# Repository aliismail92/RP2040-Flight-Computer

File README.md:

# RP2040-Flight-Computer
This is a custom drone flight computer based on RP2040. The KiCad files are available in addition to the production files to be produced by JLC PCB.

The Flight computer has the following sensors:
  - MPU 6050 Inertia sensor
  - HMC5883L digital compass sensor
  - BMP280 pressure sensor

Other specified connectors that can be added:
  - SD-card connector at the bottom of the board
  - Two uart connectors for the Radio controller (tagged IBUS) and another for GPS (tagged GPS)
  - Broken GPIOs for NRF24L01 with proper pin locations

Additionally, the two I2C ports connected to the MPU6050 and BMP280 have the pins exposed for debugging purposes.

The board was produced and assembled by JLCPCB and working.

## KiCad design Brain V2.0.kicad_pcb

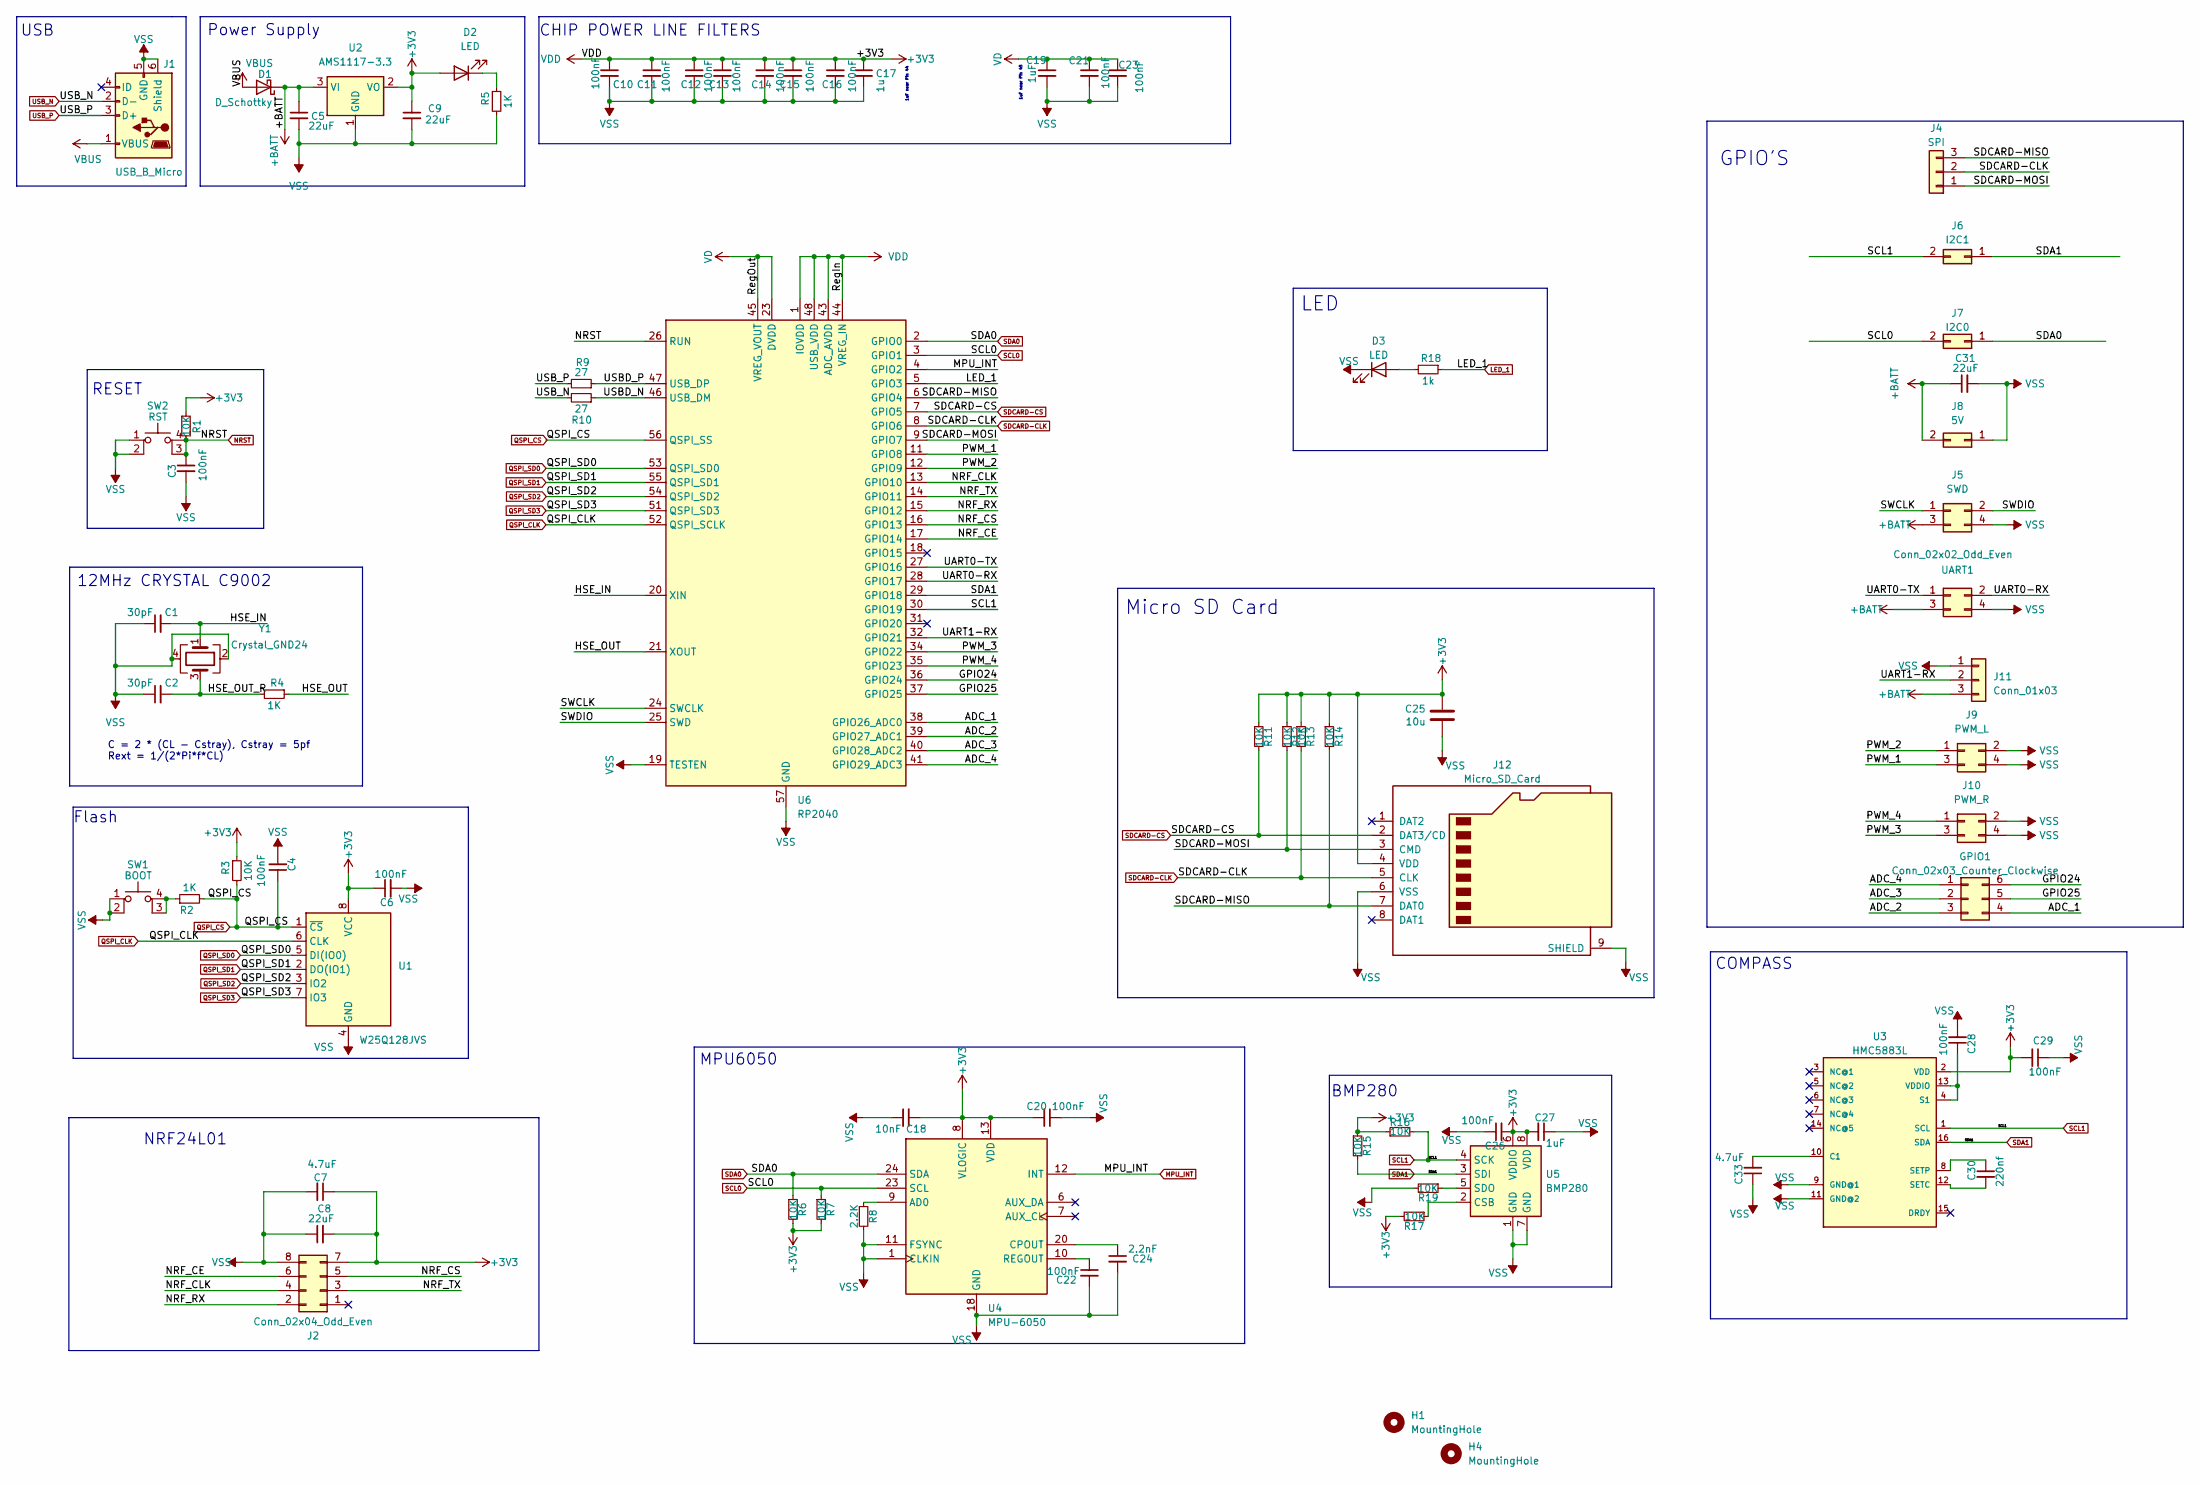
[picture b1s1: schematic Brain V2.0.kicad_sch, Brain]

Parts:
C1, C2: 30pF; C_0402_1005Metric
C3, C4, C6, C10, C11, C12, C13, C14, C15, C16, C20, C21, C22, C23, C26, C28, C29: 100nF; C_0402_1005Metric
C5, C8, C9, C31: 22uF; C_0603_1608Metric
C7, C33: 4.7uF; C_0603_1608Metric
C17: 1u; C_0402_1005Metric_Pad0.74x0.62mm_HandSolder
C18: 10nF; C_0402_1005Metric
C19: 1uF; C_0402_1005Metric_Pad0.74x0.62mm_HandSolder
C24: 2.2nF; C_0603_1608Metric
C25: 10u; C_0603_1608Metric
C27: 1uF; C_0402_1005Metric
C30: 220nf; C_0402_1005Metric
D1: D_Schottky; D_SMA
D2, D3: LED; LED_0603_1608Metric
GPIO1: Conn_02x03_Counter_Clockwise; PinHeader_2x03_P2.54mm_Vertical
H1, H4: MountingHole; MountingHole_4.3mm_M4
J1: USB_B_Micro; USB_Micro-B_Molex-105017-0001
J2: Conn_02x04_Odd_Even; PinHeader_2x04_P2.54mm_Vertical
J4: SPI; PinHeader_1x03_P2.54mm_Vertical
J5: SWD; PinHeader_2x02_P2.54mm_Vertical
J6: I2C1; PinHeader_2x01_P2.54mm_Vertical
J7: I2C0; PinHeader_2x01_P2.54mm_Vertical
J8: 5V; PinHeader_2x01_P2.54mm_Vertical
J9: PWM_L; PinHeader_2x02_P2.54mm_Vertical
J10: PWM_R; PinHeader_2x02_P2.54mm_Vertical
J11: Conn_01x03; JST_XH_B3B-XH-AM_1x03_P2.50mm_Vertical
J12: Micro_SD_Card; microSD_HC_Molex_104031-0811
R1, R3, R6, R7, R11, R12, R13, R14, R15, R16, R17, R19: 10K; R_0402_1005Metric
R2, R4: 1K; R_0402_1005Metric
R5: 1K; R_0603_1608Metric
R8: 2.2K; R_0402_1005Metric
R9, R10: 27; R_0603_1608Metric
R18: 1k; R_0603_1608Metric
SW1: BOOT; Button-01
SW2: RST; Button-01
U1: W25Q128JVS; SOIC-8_5.23x5.23mm_P1.27mm
U2: AMS1117-3.3; SOT-223-3_TabPin2
U3: HMC5883L; LPCC-16
U4: MPU-6050; InvenSense_QFN-24_4x4mm_P0.5mm_NoMask
U5: BMP280; Bosch_LGA-8_2x2.5mm_P0.65mm_ClockwisePinNumbering
U6: RP2040; QFN-56-1EP_7x7mm_P0.4mm_EP4x4mm_ThermalVias
UART1: Conn_02x02_Odd_Even; JST_XH_B4B-XH-A_1x04_P2.50mm_Vertical
Y1: Crystal_GND24; Crystal_SMD_3225-4Pin_3.2x2.5mm

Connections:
+3V3: C6.1, C7.1, C8.2, C9.1, C10.1, C11.1, C12.1, C13.1, C14.1, C15.1, C16.1, C17.1, C18.2, C20.2, C25.1, C26.2, C27.2, C29.2, D2.2 (A), J2.7, J12.4 (VDD), R1.1, R3.1, R6.2, R7.2, R11.1, R12.1, R13.1, R14.1, R15.1, R16.1, R17.2, U1.8 (VCC), U2.2 (VO), U3.2 (VDD), U4.8 (VLOGIC), U4.13 (VDD), U5.6 (VDDIO), U5.8 (VDD), U6.1 (IOVDD), U6.10 (IOVDD), U6.22 (IOVDD), U6.33 (IOVDD), U6.42 (IOVDD), U6.43 (ADC_AVDD), U6.44 (VREG_IN), U6.48 (USB_VDD), U6.49 (IOVDD)
+BATT: C5.1, C31.1, D1.1 (K), J5.3, J8.2, J11.3, U2.3 (VI), UART1.3
/ADC_1: GPIO1.4, U6.38 (GPIO26_ADC0)
/ADC_2: GPIO1.3, U6.39 (GPIO27_ADC1)
/ADC_3: GPIO1.2, U6.40 (GPIO28_ADC2)
/ADC_4: GPIO1.1, U6.41 (GPIO29_ADC3)
/GPIO24: GPIO1.6, U6.36 (GPIO24)
/GPIO25: GPIO1.5, U6.37 (GPIO25)
/HSE_IN: C1.2, U6.20 (XIN), Y1.1
/HSE_OUT: R4.1, U6.21 (XOUT)
/HSE_OUT_R: C2.2, R4.2, Y1.3
/NRF_CE: J2.6, U6.17 (GPIO14)
/NRF_CLK: J2.4, U6.13 (GPIO10)
/NRF_CS: J2.5, U6.16 (GPIO13)
/NRF_RX: J2.2, U6.15 (GPIO12)
/NRF_TX: J2.3, U6.14 (GPIO11)
/PWM_1: J9.3, U6.11 (GPIO8)
/PWM_2: J9.1, U6.12 (GPIO9)
/PWM_3: J10.3, U6.34 (GPIO22)
/PWM_4: J10.1, U6.35 (GPIO23)
/SDCARD-MISO: J4.3, J12.7 (DAT0), R14.2, U6.6 (GPIO4)
/SDCARD-MOSI: J4.1, J12.3 (CMD), R12.2, U6.9 (GPIO7)
/SWCLK: J5.1, U6.24 (SWCLK)
/SWDIO: J5.2, U6.25 (SWD)
/UART0-RX: U6.28 (GPIO17), UART1.2
/UART0-TX: U6.27 (GPIO16), UART1.1
/UART1-RX: J11.2, U6.32 (GPIO21)
/USBD_N: R10.1, U6.46 (USB_DM)
/USBD_P: R9.1, U6.47 (USB_DP)
LED_1: R18.1, U6.5 (GPIO3)
MPU_INT: U4.12 (INT), U6.4 (GPIO2)
NRST: C3.1, R1.2, SW2.3 (K), SW2.4 (A), U6.26 (RUN)
unnamed: D2.1 (K), R5.1
unnamed: D3.2 (A), R18.2
unnamed: R2.1, SW1.3 (K), SW1.4 (A)
unnamed: C33.2, U3.10 (C1)
unnamed: C28.1, U3.4 (S1), U3.13 (VDDIO)
unnamed: C30.2, U3.12 (SETC)
unnamed: C30.1, U3.8 (SETP)
unnamed: R8.1, U4.9 (AD0)
unnamed: C24.1, U4.20 (CPOUT)
unnamed: C22.1, U4.10 (REGOUT)
unnamed: R17.1, U5.2 (CSB)
unnamed: R19.1, U5.5 (SDO)
QSPI_CLK: U1.6 (CLK), U6.52 (QSPI_SCLK)
QSPI_CS: C4.1, R2.2, R3.2, U1.1 (~CS), U6.56 (QSPI_SS)
QSPI_SD0: U1.5 (DI(IO0)), U6.53 (QSPI_SD0)
QSPI_SD1: U1.2 (DO(IO1)), U6.55 (QSPI_SD1)
QSPI_SD2: U1.3 (IO2), U6.54 (QSPI_SD2)
QSPI_SD3: U1.7 (IO3), U6.51 (QSPI_SD3)
SCL0: J7.2, R7.1, U4.23 (SCL), U6.3 (GPIO1)
SCL1: J6.2, R16.2, U3.1 (SCL), U5.4 (SCK), U6.30 (GPIO19)
SDA0: J7.1, R6.1, U4.24 (SDA), U6.2 (GPIO0)
SDA1: J6.1, R15.2, U3.16 (SDA), U5.3 (SDI), U6.29 (GPIO18)
SDCARD-CLK: J4.2, J12.5 (CLK), R13.2, U6.8 (GPIO6)
SDCARD-CS: J12.2 (DAT3/CD), R11.2, U6.7 (GPIO5)
USB_N: J1.2 (D-), R10.2
USB_P: J1.3 (D+), R9.2
VBUS: D1.2 (A), J1.1 (VBUS)
VD: C19.1, C21.1, C23.1, U6.23 (DVDD), U6.45 (VREG_VOUT), U6.50 (DVDD)
VSS: C1.1, C2.1, C3.2, C4.2, C5.2, C6.2, C7.2, C8.1, C9.2, C10.2, C11.2, C12.2, C13.2, C14.2, C15.2, C16.2, C17.2, C18.1, C19.2, C20.1, C21.2, C22.2, C23.2, C24.2, C25.2, C26.1, C27.1, C28.2, C29.1, C31.2, C33.1, D3.1 (K), J1.5 (GND), J1.6 (Shield), J2.8, J5.4, J8.1, J9.2, J9.4, J10.2, J10.4, J11.1, J12.6 (VSS), J12.9 (SHIELD), R5.2, R8.2, R19.2, SW1.1, SW1.2, SW2.1, SW2.2, U1.4 (GND), U2.1 (GND), U3.9 (GND@1), U3.11 (GND@2), U4.1 (CLKIN), U4.11 (FSYNC), U4.18 (GND), U5.1 (GND), U5.7 (GND), U6.19 (TESTEN), U6.57 (GND), UART1.4, Y1.2, Y1.4

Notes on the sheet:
RESET
GPIO'S
1uF near Pin 45
MPU6050
CHIP POWER LINE FILTERS
BMP280
12MHz CRYSTAL C9002
LED
Micro SD Card
COMPASS
NRF24L01
Flash
C = 2 * (CL - Cstray), Cstray = 5pf Rext = 1/(2*Pi*f*CL)
Power Supply
USB
1uF near Pin 44

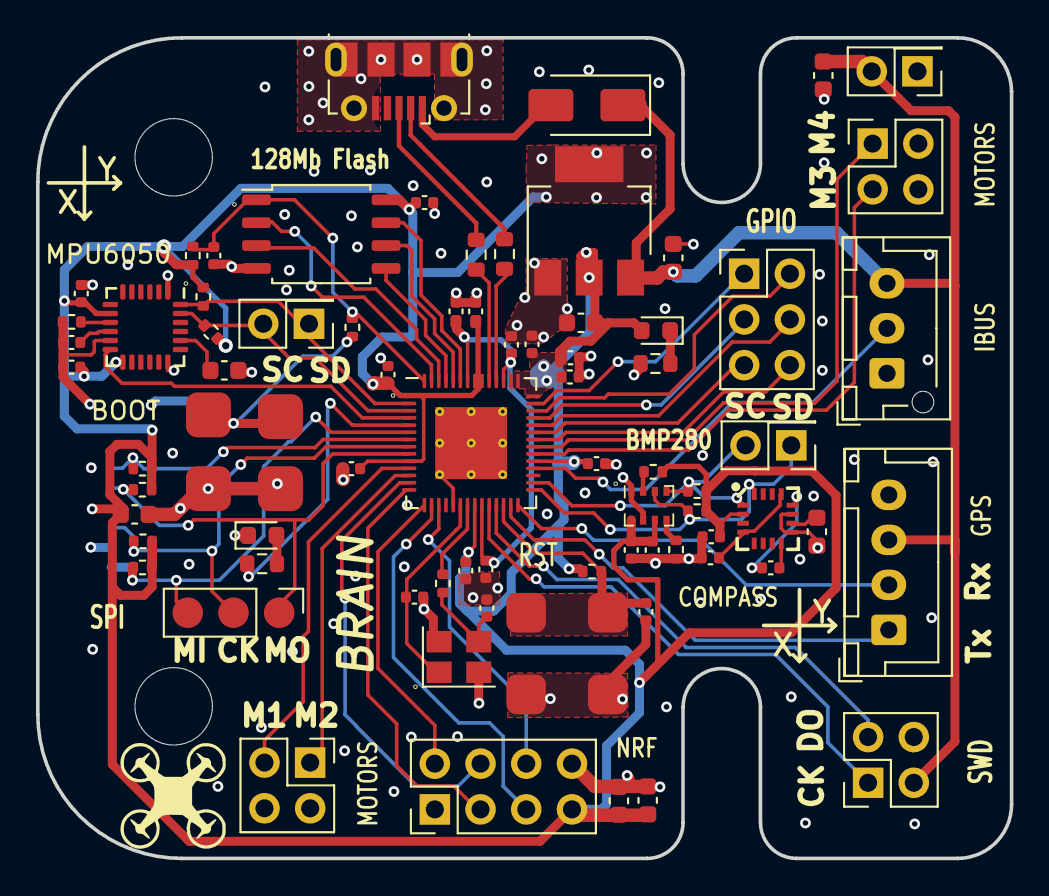
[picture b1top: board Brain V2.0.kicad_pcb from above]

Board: 4 copper layers, 54.1 x 45.6 mm, 78 parts (1 on the bottom side), 61 nets.

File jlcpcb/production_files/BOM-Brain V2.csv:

Comment,Designator,Footprint,LCSC
1K,"R2,R4",R_0402_1005Metric,C11702
USB_B_Micro,J1,USB_Micro-B_Molex-105017-0001,C136000
10nF,C18,C_0402_1005Metric,C15195
100nF,"C10,C11,C12,C13,C14,C15,C16,C20,C21,C22,C23,C26,C28,C29,C3,C4,C6",C_0402_1005Metric,C1525
30pF,"C1,C2",C_0402_1005Metric,C1562
2.2nF,C24,C_0603_1608Metric,C1604
220nf,C30,C_0402_1005Metric,C16772
4.7uF,"C33,C7",C_0603_1608Metric,C19666
10u,C25,C_0603_1608Metric,C19702
RP2040,U6,QFN-56-1EP_7x7mm_P0.4mm_EP4x4mm_ThermalVias,C2040
1k,"R18,R5",R_0603_1608Metric,C21190
LED,"D2,D3",LED_0603_1608Metric,C2290
MPU-6050,U4,InvenSense_QFN-24_4x4mm_P0.5mm_NoMask,C24112
27,"R10,R9",R_0603_1608Metric,C25190
10K,"R1,R11,R12,R13,R14,R15,R16,R17,R19,R3,R6,R7",R_0402_1005Metric,C25744
2.2K,R8,R_0402_1005Metric,C25879
D_Schottky,D1,D_SMA,C2909963
1u,"C17,C19,C27",C_0402_1005Metric_Pad0.74x0.62mm_HandSolder,C52923
22uF,"C31,C5,C8,C9",C_0603_1608Metric,C59461
AMS1117-3.3,U2,SOT-223-3_TabPin2,C6186
BMP280,U5,Bosch_LGA-8_2x2.5mm_P0.65mm_ClockwisePinNumbering,C83291
Crystal_GND24,Y1,Crystal_SMD_3225-4Pin_3.2x2.5mm,C9002
W25Q128JVS,U1,SOIC-8_5.23x5.23mm_P1.27mm,C97521
